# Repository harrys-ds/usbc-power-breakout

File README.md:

# USB-C Power Breakout

A small breadboard-friendly board that takes power from any USB-C charger and provides regulated **5 V** and **3.3 V** outputs, with a power indicator LED. Designed in KiCad as my first PCB.

> Status: 🛠️ In progress — schematic stage

## Features
- USB-C input that works with USB-C-to-C chargers (5.1 kΩ CC pull-downs)
- 3.3 V output, up to 600 mA (AP2112K-3.3 LDO)
- 5 V pass-through output
- Power-on LED
- 0805 passives for easy hand soldering

## Block diagram
<!-- Add an image: docs/block-diagram.png -->
`USB-C → (5 V rail) → LED indicator`
`               └──→ AP2112K LDO → (3.3 V rail)`
`Both rails + GND → pin header`

## Schematic
<!-- Export from KiCad: File → Plot → PDF, save to docs/schematic.pdf, and add a PNG here -->

## PCB
<!-- Add 3D view render and front/back photos -->

## Bill of materials
| Ref | Part | Value / Package | Qty |
|---|---|---|---|
| J1 | USB-C receptacle | power-only | 1 |
| R1, R2 | Resistor | 5.1 kΩ, 0805 | 2 |
| R3 | Resistor | 1 kΩ, 0805 | 1 |
| D1 | LED | red, 0805 | 1 |
| U1 | LDO regulator | AP2112K-3.3, SOT-23-5 | 1 |
| C1, C2 | Capacitor | 1 µF, 0805 | 2 |
| J2 | Pin header | 1x03, 2.54 mm | 1 |

## What I learned / problems I hit 
<!-- Fill this in as you go. This is the section recruiters actually read. -->
- Making a clean power supply
- starting with "USB_C_Receptacle_PowerOnly_6P"
- VBUS: The 5v coming from charger
- GND: Ground
- CC1, CC2: Handshake pins
- SHIELD: metal shell of connector.

- power led
-   lights up whenever 5v is present
-   if resistor wasn't there it would burn out

- 3.3v regulator, less power 
-   takes 5v in and holds it at 3.3v
-   ap2112k is a LDO, constantly adjusts voltage to keep output at 3.3v
-   dropped voltage turns to heat - a tradeoff
-   EN: regulator only runs when EN is high, tying to VIN means it switches on when power arrives.
- The two µF capacitors
-   C2: tiny energy reserve - covers sudden current demands the USB cable can't respond to fast enough (VIN stabilization) 
-   C1: keeps regulator stable & smooths 3.3v output when load changes.
- Output Header (J2)
-   +5v - for 5v devices 
-   +3v3 - devices such as ESP32 or RP2040
-   GND - return path for both

- 5v pin is raw usb power, 3.3 is more regulated.

## Testing
<!-- Measured output voltages, which chargers it worked with, etc. -->

## Files
- `usbc-power-breakout.kicad_sch` — schematic
- `usbc-power-breakout.kicad_pcb` — PCB layout
- `fabrication/` — Gerbers sent to the fab (added once ordered)

## Tools
KiCad · Multimeter · Soldering station

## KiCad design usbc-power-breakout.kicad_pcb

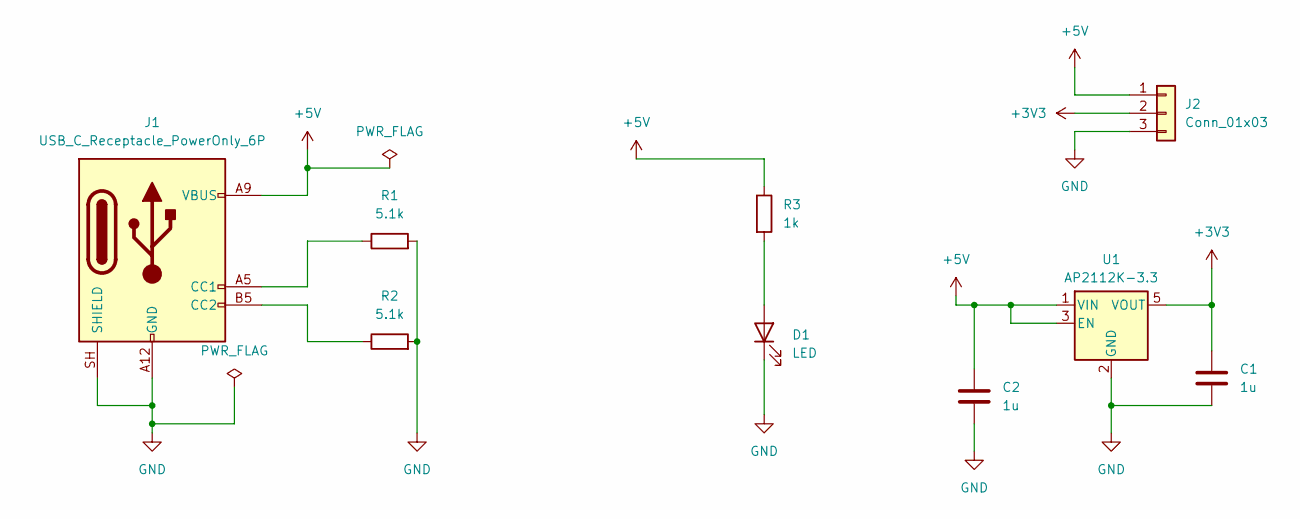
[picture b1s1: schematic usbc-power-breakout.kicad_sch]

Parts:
C1, C2: 1u; C_0805_2012Metric
D1: LED; LED_0805_2012Metric
J1: USB_C_Receptacle_PowerOnly_6P; USB_C_Receptacle_GCT_USB4125-xx-x_6P_TopMnt_Horizontal
J2: Conn_01x03; PinHeader_1x03_P2.54mm_Vertical
R1, R2: 5.1k; R_0805_2012Metric
R3: 1k; R_0805_2012Metric
U1: AP2112K-3.3; SOT-23-5

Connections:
+3V3: C1.1, J2.2, U1.5 (VOUT)
+5V: C2.1, J1.A9 (VBUS), J1.B9 (VBUS), J2.1, R3.1, U1.1 (VIN), U1.3 (EN)
GND: C1.2, C2.2, D1.1 (K), J1.A12 (GND), J1.B12 (GND), J1.SH (SHIELD), J2.3, R1.2, R2.2, U1.2 (GND)
unnamed: D1.2 (A), R3.2
unnamed: J1.A5 (CC1), R1.1
unnamed: J1.B5 (CC2), R2.1

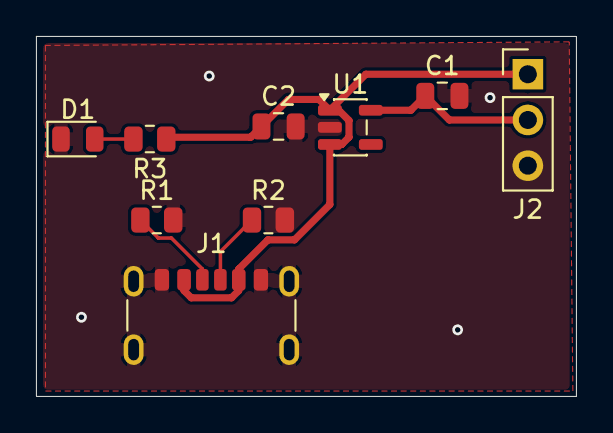
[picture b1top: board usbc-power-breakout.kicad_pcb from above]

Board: 2 copper layers, 30.0 x 20.0 mm, 9 parts (0 on the bottom side), 6 nets.
